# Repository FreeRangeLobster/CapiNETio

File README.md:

# CapiNETio

##To Do List:
* [x]Update all models
*[x] OK Add a new power connector 2 poles
*[x] OK Add a switch to allow power from the bus
*[x] OK Replace the 2 bus strips for one single one
*[x] OK create the layout and angle the in/Out Connectors
*[x] OK Check type of components and pcb constrains
*[]🔥  Show pull-up vs pull-down drive best practice

# Microcontroller

***Dip Switch
10 kΩ pull-up resistors (standard value)
Per input:
3.3V ── 10kΩ ── GPIO pin ── switch ── GND

Microcontroller output max per pin 

IO
Page73 of datasheet
Output current sunk by any I/O and control pin 25
Output current sourced by any I/Os and control pin - 25

LED current consumption
10ma

***LED indicators
Typical LED (553-0122F – red indicator)
Approximate specs (common for this part family):
• Forward voltage Vf ≈ 1.9–2.1 V
• Good brightness at 5–10 mA (no need to push 20 mA on STM32 pins)
STM32 GPIO max per pin is usually ~20 mA absolute max, but 5–8 mA is best practice.
Resistor calculation (3.3 V pin)
At 10 mA:
R = (3.3 − 2.0) / 0.01 = 130 Ω
At 5 mA (recommended for MCU safety):
R = (3.3 − 2.0) / 0.005 = 260 Ω

Best real-world values
Current	Resistor
~10 mA	150 Ω
~6 mA	220 Ω
~4 mA	330 Ω
use 220 Ω — bright enough and easy on the STM32 pin
   330 Ω if you want conservative current
Wiring
PA4 → resistor → LED → GND
(or LED to 3.3 V and pin sinks current — both fine)
⚠️ Important STM32
Try to keep:
≤ 8 mA per pin
≤ 100 mA total for the whole GPIO port

## Programming

# Power Supply

# RS485 bus

# Serial Comms

## Serial Comms USB
## Serial Comms

# Outputs

outputs relay, the LED calculations:
Device	Vf
551-0207-004F LED	~2.0 V
TLP290 LED	~1.2 V
Total	~3.2 V

STM32 output = 3.3 V

⚠️ T.hat leaves only:

3.3 − 3.2 = 0.1 V
not a good idea to put them in series. so need to be in parallel
GPIO → 390Ω → TLP290 LED → GND
GPIO → 1kΩ  → indicator LED → GND

# Inputs
***Inputs 5 to 24V. Pin3 inputs needs to be 0V common :

1.5 kΩ, 0.5 W resistor
5.1 V Zener diode (0.25 W or higher)
LEDs in series (indicator + opto)

indicator LED (551-0207-004F) in series with the TLP290 LED and a requirement that it must reliably turn ON already at 5 V, we should bias this a bit stronger than the “borderline” case and still keep it safe at 24 V.

 Known drops (worst-case friendly)

Typical at a few mA:

• Indicator LED ≈ 2.0 V
• TLP290 LED ≈ 1.2 V

👉 Total ≈ 3.2 V

🎯 Target currents

To guarantee turn-on across temperature & aging:

✅ Minimum at 5 V → ≈2 mA
✅ Normal at 24 V → 6–10 mA

This keeps CTR healthy and LEDs safe.

🧩 Use Zener clamp (still the right approach)

Clamp voltage: 5.1 V

So effective resistor voltage at clamp:

5.1 − 3.2 = 1.9 V

🧮 Pick resistor for strong low-end + safe high-end

Let’s choose R = 1.5 kΩ (this is the sweet spot now).

📊 Check operation
✅ At 5 V input (no heavy clamp yet):
I ≈ (5 − 3.2) / 1.5k ≈ 1.2 mA

Plus clamp assistance as it approaches 5.1 V → roughly 1.5–2 mA effective

Enough to switch TLP290 reliably.

✅ At 24 V input (clamped):
I ≈ (24 − 5.1) / 1.5k ≈ 12.6 mA

Still within safe continuous LED current.

Power check (important)

Resistor:

P ≈ I²R ≈ (0.0126)² × 1500 ≈ 0.24 W

👉 Use ½ W resistor (recommended for longevity)

Zener:

P ≈ 5.1 × 0.0126 ≈ 64 mW

Any 0.25 W zener is fine.

✅ Final rugged values (guaranteed 5–24 V)
Input side:

🟢 1.5 kΩ, 0.5 W resistor
🟢 5.1 V Zener diode (0.25 W or higher)
🟢 LEDs in series (indicator + opto)

📌 Conclusion

✔ Turns ON at 5 V every time
✔ Safe at 24 V continuously
✔ Good noise margin
✔ Long LED life

Good to Add:
✔️ Add reverse polarity protection diode
✔️ Add surge suppressor (TVS)
✔️ Show exact schematic symbol placement

Zener options:

Here are some **good SMD Zener diode options you can use as your 5.1 V clamp on the input side of your optocoupler circuit (to clamp voltage around ~5.1 V for a 1.5 kΩ series resistor):

Nexperia BZX884‑C5V1 Zener Diode
€0.19
•
JAK Electronics + others
onsemi MMBZ5231ELT1G Zener Diode
€0.26
•
DigiKey Italy
DiodesZetex 5.1V Zener (SMD)
€0.26
•
DigiKey Italy
Vishay BZM55C5V1TR MicroMELF Zener
€0.17
•
DigiKey Italy + others
ROHM PDZVTFTR5.1B Zener Diode
€0.39
•
Mouser Italia
ROHM KDZVTFTR5.1B Zener Diode
€0.54
•
Mouser Italia
onsemi 1SMB5918BT3G 5.1 V Zener
€0.64
•
Mouser Italia
Vishay AEC‑Q101 5.1 V Zener (automotive)
€15.80
•
RS Italy
🟡 Best general-purpose low-power (0.25–0.35 W)

These are ideal for clamping in your optocoupler input. Typical power rating ~250–350 mW which is enough for ~5–10 mA clamp:

Nexperia BZX884‑C5V1 Zener Diode – SOT-23, very common, cheap, 5.1 V clamp.

onsemi MMBZ5231ELT1G Zener Diode – another SOT-23 5.1 V option at low cost.

DiodesZetex 5.1V Zener (SMD) – generic 5.1 V Zener in compact SMD package.

Vishay BZM55C5V1TR MicroMELF Zener – MicroMELF style, tiny but robust.

ROHM PDZVTFTR5.1B Zener Diode – well-known brand part.

🟢 Higher power / automotive or robust

If you want more clamp headroom or automotive spec:

ROHM KDZVTFTR5.1B Zener Diode – similar to above with slightly different rating.

onsemi 1SMB5918BT3G 5.1 V Zener – much higher power, overkill for this but good for surge protection too.

Vishay AEC‑Q101 5.1 V Zener (automotive) – automotive-grade if you need rugged industrial reliability.

📌 How to choose

✔ For typical PCB input clamping and currents ~5-10 mA: go with BZX884-C5V1 or MMBZ5231ELT1G in SOT-23 — they are small, cheap, and easy to place.
✔ For power handling or are worried about surges, pick a 500 mW part like ROHM or larger packages.

BZX884-C5V1

D1 – SS14 / BAT54 (Schottky)
R1 – 1.5kΩ 0.5W
ZD1 – 5.1V SMD Zener (SOT-23 or SOD-123)
R2 – 10kΩ
LED1 – 551-0207-004F
LED2 – TLP290

# Cheat sheet

git push -u origin main

Kicad tutorial stm32
https://www.youtube.com/watch?v=aVUqaB0IMh4
KiCad 6 STM32 PCB Design Full Tutorial - Phil's Lab #65

Songs:

nati botero te quiero mucho, ponka el problemon, no todo puede llamarse amor jorge celedon, todo de cabeza, la indiferencia de silvestre dangon, labios compartidos, amor de verano eddie, pump it black eyed peas, sexy back justin, i wann love you akon, crazy knarrls barkley, gwen stefany sh=weetes, rehab amy winehouse, bad date daniel, welcome to the black parade, supermassive blackhole muse, snow red hot chilly pepers,

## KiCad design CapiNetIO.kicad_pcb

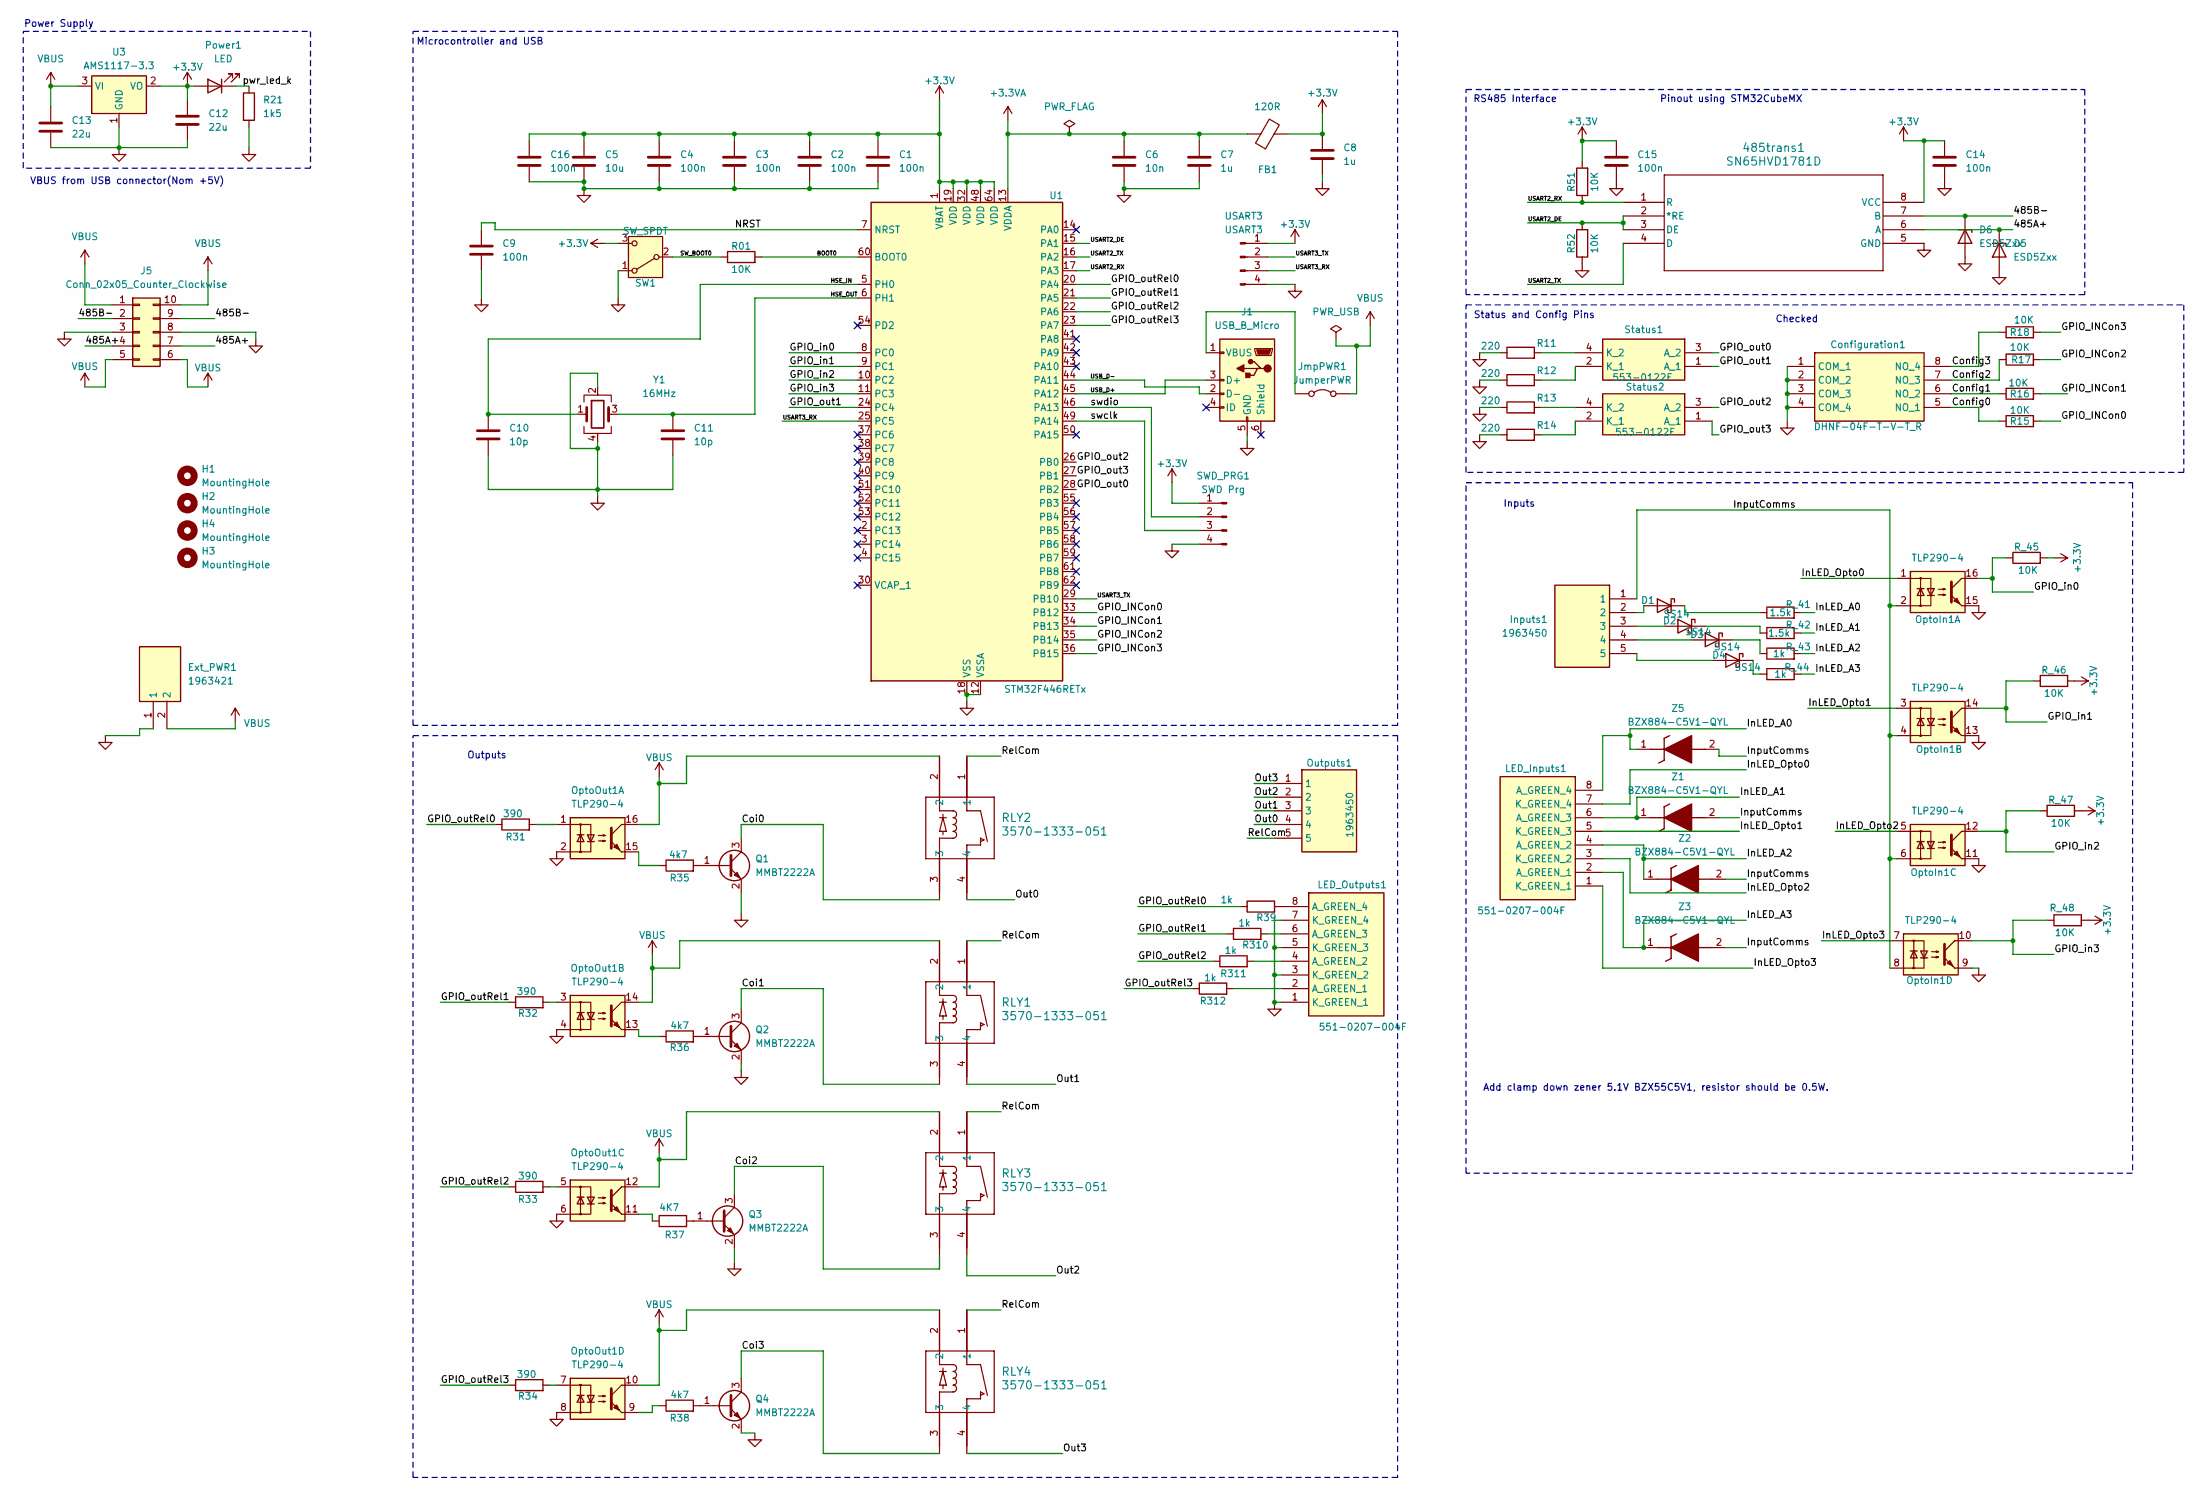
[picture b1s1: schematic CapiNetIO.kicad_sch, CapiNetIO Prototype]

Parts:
485trans1: SN65HVD1781D
C1, C2, C3, C4, C9, C14, C15, C16: 100n; C_0603_1608Metric
C5: 10u; C_0603_1608Metric
C6: 10n; C_0603_1608Metric
C7, C8: 1u; C_0603_1608Metric
C10, C11: 10p; C_0603_1608Metric
C12, C13: 22u; C_0805_2012Metric
Configuration1: DHNF-04F-T-V-T_R; DHNF04FTVTR; Mouser Part Number 113-DHNF04FTVTR
D1, D2, D3, D4: SS14; D_SMA
D5, D6: ESD5Zxx; D_SOD-523
Ext_PWR1: 1963421; Manufacturer_Part_Number 1963421
FB1: 120R; L_0603_1608Metric
H1, H2, H3, H4: MountingHole; MountingHole_3.5mm
Inputs1: 1963450; Manufacturer_Part_Number 1963450; Mouser Part Number 651-1963450
J1: USB_B_Micro; USB_Micro-B_Wuerth_629105150521
J5: Conn_02x05_Counter_Clockwise; IDC-Header_2x05_P2.54mm_Vertical
JmpPWR1: JumperPWR; TestPoint_2Pads_Pitch2.54mm_Drill0.8mm
LED_Inputs1: 551-0207-004F; 5510207004F; Manufacturer_Part_Number 551-0207-004F
LED_Outputs1: 551-0207-004F; 5510207004F; Manufacturer_Part_Number 551-0207-004F
OptoIn1: TLP290-4; SOP-16_4.55x10.3mm_P1.27mm
OptoOut1: TLP290-4; SOP-16_4.55x10.3mm_P1.27mm
Outputs1: 1963450; Manufacturer_Part_Number 1963450; Mouser Part Number 651-1963450
Power1: LED; LED_0603_1608Metric
Q1, Q2, Q3, Q4: MMBT2222A; SOT-23
R01, R15, R16, R17, R18, R51, R52: 10K; R_0402_1005Metric
R11, R12, R13, R14: 220; R_0402_1005Metric
R21: 1k5; R_0402_1005Metric
R31, R32, R33, R34: 390; R_0402_1005Metric
R35, R36, R38: 4k7; R_0402_1005Metric
R37: 4K7; R_0402_1005Metric
R39, R310, R311, R312: 1k; R_0402_1005Metric
RLY1, RLY2, RLY3, RLY4: 3570-1333-051; RELAY4_3570-1333-051_COM
R_41, R_42: 1.5k; R_0402_1005Metric
R_43, R_44: 1k; R_0402_1005Metric
R_45, R_46, R_47, R_48: 10K; R_0402_1005Metric
SW1: SW_SPDT; SW_SPDT_PCM12
SWD_PRG1: SWD Prg; PinHeader_1x04_P2.54mm_Horizontal
Status1, Status2: 553-0122F; 5530122F; Mouser Part Number 645-553-0122F
U1: STM32F446RETx; LQFP-64_10x10mm_P0.5mm
U3: AMS1117-3.3; SOT-223-3_TabPin2
USART3: USART3; PinHeader_1x04_P2.54mm_Horizontal
Y1: 16MHz; Crystal_SMD_3225-4Pin_3.2x2.5mm
Z1, Z2, Z3, Z5: BZX884-C5V1-QYL; BZX884C5V1QYL; Manufacturer_Part_Number BZX884-C5V1-QYL

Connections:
+3.3V: 485trans1.8 (VCC), C1.1, C2.1, C3.1, C4.1, C5.1, C8.1, C12.1, C14.1, C15.1, C16.1, FB1.2, Power1.2 (A), R51.2, R_45.2, R_46.2, R_47.2, R_48.2, SW1.3 (C), SWD_PRG1.1, U1.1 (VBAT), U1.19 (VDD), U1.32 (VDD), U1.48 (VDD), U1.64 (VDD), U3.2 (VO), USART3.1
+3.3VA: C6.1, C7.1, FB1.1, U1.13 (VDDA)
/485A+: 485trans1.6 (A), D5.1 (K), J5.4, J5.7
/485B-: 485trans1.7 (B), D6.1 (K), J5.2, J5.9
/BOOT0: R01.2, U1.60 (BOOT0)
/Coi0: Q1.3 (C), RLY2.3
/Coi1: Q2.3 (C), RLY1.3
/Coi2: Q3.3 (C), RLY3.3
/Coi3: Q4.3 (C), RLY4.3
/Config0: Configuration1.5 (NO_1), R15.1
/Config1: Configuration1.6 (NO_2), R16.1
/Config2: Configuration1.7 (NO_3), R17.1
/Config3: Configuration1.8 (NO_4), R18.1
/GPIO_INCon0: R15.2, U1.33 (PB12)
/GPIO_INCon1: R16.2, U1.34 (PB13)
/GPIO_INCon2: R17.2, U1.35 (PB14)
/GPIO_INCon3: R18.2, U1.36 (PB15)
/GPIO_in0: OptoIn1.16, R_45.1, U1.8 (PC0)
/GPIO_in1: OptoIn1.14, R_46.1, U1.9 (PC1)
/GPIO_in2: OptoIn1.12, R_47.1, U1.10 (PC2)
/GPIO_in3: OptoIn1.10, R_48.1, U1.11 (PC3)
/GPIO_out0: Status1.3 (A_2), U1.28 (PB2)
/GPIO_out1: Status1.1 (A_1), U1.24 (PC4)
/GPIO_out2: Status2.3 (A_2), U1.26 (PB0)
/GPIO_out3: Status2.1 (A_1), U1.27 (PB1)
/GPIO_outRel0: R31.1, R39.1, U1.20 (PA4)
/GPIO_outRel1: R32.1, R310.1, U1.21 (PA5)
/GPIO_outRel2: R33.1, R311.1, U1.22 (PA6)
/GPIO_outRel3: R34.1, R312.1, U1.23 (PA7)
/HSE_IN: C10.1, U1.5 (PH0), Y1.1
/HSE_OUT: C11.1, U1.6 (PH1), Y1.3
/InLED_A0: LED_Inputs1.8 (A_GREEN_4), R_41.2, Z5.1 (K)
/InLED_A1: LED_Inputs1.6 (A_GREEN_3), R_42.2, Z1.1 (K)
/InLED_A2: LED_Inputs1.4 (A_GREEN_2), R_43.2, Z2.1 (K)
/InLED_A3: LED_Inputs1.2 (A_GREEN_1), R_44.2, Z3.1 (K)
/InLED_Opto0: LED_Inputs1.7 (K_GREEN_4), OptoIn1.1
/InLED_Opto1: LED_Inputs1.5 (K_GREEN_3), OptoIn1.3
/InLED_Opto2: LED_Inputs1.3 (K_GREEN_2), OptoIn1.5
/InLED_Opto3: LED_Inputs1.1 (K_GREEN_1), OptoIn1.7
/InputComms: Inputs1.1, OptoIn1.2, OptoIn1.4, OptoIn1.6, OptoIn1.8, Z1.2 (A), Z2.2 (A), Z3.2 (A), Z5.2 (A)
/NRST: C9.1, U1.7 (NRST)
/Out0: Outputs1.4, RLY2.4
/Out1: Outputs1.3, RLY1.4
/Out2: Outputs1.2, RLY3.4
/Out3: Outputs1.1, RLY4.4
/RelCom: Outputs1.5, RLY1.1, RLY2.1, RLY3.1, RLY4.1
/SW_BOOT0: R01.1, SW1.2 (B)
/USART2_DE: 485trans1.2 (*RE), 485trans1.3 (DE), R52.2, U1.15 (PA1)
/USART2_RX: 485trans1.1 (R), R51.1, U1.17 (PA3)
/USART2_TX: 485trans1.4 (D), U1.16 (PA2)
/USART3_RX: U1.25 (PC5), USART3.3
/USART3_TX: U1.29 (PB10), USART3.2
/USB_D+: J1.3 (D+), U1.45 (PA12)
/USB_D-: J1.2 (D-), U1.44 (PA11)
/pwr_led_k: Power1.1 (K), R21.1
/swclk: SWD_PRG1.3, U1.49 (PA14)
/swdio: SWD_PRG1.2, U1.46 (PA13)
GND: 485trans1.5 (GND), C1.2, C2.2, C3.2, C4.2, C5.2, C6.2, C7.2, C8.2, C9.2, C10.2, C11.2, C12.2, C13.2, C14.2, C15.2, C16.2, Configuration1.1 (COM_1), Configuration1.2 (COM_2), Configuration1.3 (COM_3), Configuration1.4 (COM_4), D5.2 (A), D6.2 (A), Ext_PWR1.1, J1.5 (GND), J5.3, J5.8, LED_Outputs1.1 (K_GREEN_1), LED_Outputs1.3 (K_GREEN_2), LED_Outputs1.5 (K_GREEN_3), LED_Outputs1.7 (K_GREEN_4), OptoIn1.9, OptoIn1.11, OptoIn1.13, OptoIn1.15, OptoOut1.2, OptoOut1.4, OptoOut1.6, OptoOut1.8, Q1.2 (E), Q2.2 (E), Q3.2 (E), Q4.2 (E), R11.1, R12.1, R13.1, R14.1, R21.2, R52.1, SW1.1 (A), SWD_PRG1.4, U1.12 (VSSA), U1.18 (VSS), U1.31 (VSS), U1.47 (VSS), U1.63 (VSS), U3.1 (GND), USART3.4, Y1.2, Y1.4
unnamed: D1.2 (A), Inputs1.2
unnamed: D1.1 (K), R_41.1
unnamed: D2.2 (A), Inputs1.3
unnamed: D2.1 (K), R_42.1
unnamed: D3.2 (A), Inputs1.4
unnamed: D3.1 (K), R_43.1
unnamed: D4.2 (A), Inputs1.5
unnamed: D4.1 (K), R_44.1
unnamed: J1.1 (VBUS), JmpPWR1.1 (A)
unnamed: LED_Outputs1.2 (A_GREEN_1), R312.2
unnamed: LED_Outputs1.4 (A_GREEN_2), R311.2
unnamed: LED_Outputs1.6 (A_GREEN_3), R310.2
unnamed: LED_Outputs1.8 (A_GREEN_4), R39.2
unnamed: OptoOut1.1, R31.2
unnamed: OptoOut1.3, R32.2
unnamed: OptoOut1.5, R33.2
unnamed: OptoOut1.7, R34.2
unnamed: OptoOut1.9, R38.1
unnamed: OptoOut1.11, R37.1
unnamed: OptoOut1.13, R36.1
unnamed: OptoOut1.15, R35.1
unnamed: Q1.1 (B), R35.2
unnamed: Q2.1 (B), R36.2
unnamed: Q3.1 (B), R37.2
unnamed: Q4.1 (B), R38.2
unnamed: R12.2, Status1.2 (K_1)
unnamed: R11.2, Status1.4 (K_2)
unnamed: R14.2, Status2.2 (K_1)
unnamed: R13.2, Status2.4 (K_2)
VBUS: C13.1, Ext_PWR1.2, J5.1, J5.5, J5.6, J5.10, JmpPWR1.2 (B), OptoOut1.10, OptoOut1.12, OptoOut1.14, OptoOut1.16, RLY1.2, RLY2.2, RLY3.2, RLY4.2, U3.3 (VI)

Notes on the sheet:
Microcontroller and USB
Power Supply
VBUS from USB connector(Nom +5V)
Pinout using STM32CubeMX
Status and Config Pins
Add clamp down zener 5.1V BZX55C5V1, resistor should be 0.5W.
Inputs
Checked
Outputs
RS485 Interface

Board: 2 copper layers, 92 parts (0 on the bottom side), 88 nets, no tracks yet.

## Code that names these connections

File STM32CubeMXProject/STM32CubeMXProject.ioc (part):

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Mcu.Name=STM32F446R(C-E)Tx
Mcu.Package=LQFP64
Mcu.UserName=STM32F446RETx
PA13.Mode=Serial_Wire
PA13.Signal=SYS_JTMS-SWDIO
PA14.Mode=Serial_Wire
PA14.Signal=SYS_JTCK-SWCLK
PB0.Signal=GPIO_Output
PB1.Signal=GPIO_Output
PB2.Signal=GPIO_Output
PC0.Signal=GPIO_Input
PC1.Signal=GPIO_Input
PC2.Signal=GPIO_Input
PC3.Signal=GPIO_Input
PC4.Signal=GPIO_Output
board=custom

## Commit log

2026-01-23 checking components are present in pcb and renaming
2026-01-28 Updating models
2026-01-31 Status and dipswitches, checked, working on inputs
2026-02-02 checked outputs for resistors and circuits
2026-02-03 updated inter PCB bus, added jumper power from USB
2026-02-04 Overall Check, need to update the pbc constrains to pass checks
2026-02-09 Checked footprints and pcb constrains, time to start tracing
2026-02-09 tidy up readme
2026-02-16 Changed pins GPIO_Out0-3 and GPIO_In0-3 to a more accessible ones. Added project CubeMX
2026-02-17 working on the pcb side, tidying up io
